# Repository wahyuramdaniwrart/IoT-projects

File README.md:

# Project IoT WRART

## Descriptions
Selamat Datang di project IoT yang saya jalankan, ini merupakan arsip dar setiap project yang sudah saya jalankan, silahkan gunakan dengan sebaik mungkin jika memang source kode yang digunakan pada poject ini bisa bermanfaat unuk anda. project ini menggunakan eagle untuk membuat wiring dan skema rangkaian alatnya.

## Contributing
Kami menyambut semua kontribusi! Berikut ini beberapa cara untuk memulai:
1. Laporkan bug: Jika Anda menemukan bug, harap beri tahu kami. Ajukan masalah dan beri tahu kami masalahnya.
2. Kontribusikan kode: Jika Anda seorang pengembang dan ingin berkontribusi, ikuti petunjuk di bawah ini untuk memulai!
3. Saran: Jika Anda tidak ingin membuat kode tetapi memiliki beberapa ide hebat, ajukan masalah yang menjelaskan beberapa pembaruan atau peningkatan yang ingin Anda lihat!
4. Dokumentasi: Jika Anda merasa perlu beberapa dokumentasi tambahan, jangan ragu untuk menambahkannya!

## Instructions
1. Fork repositori ini
2. Klon repositori yang di-fork
3. Tambahkan kontribusi Anda (kode atau dokumentasi)
4. Commit dan push
5. Tunggu hingga pull request digabungkan

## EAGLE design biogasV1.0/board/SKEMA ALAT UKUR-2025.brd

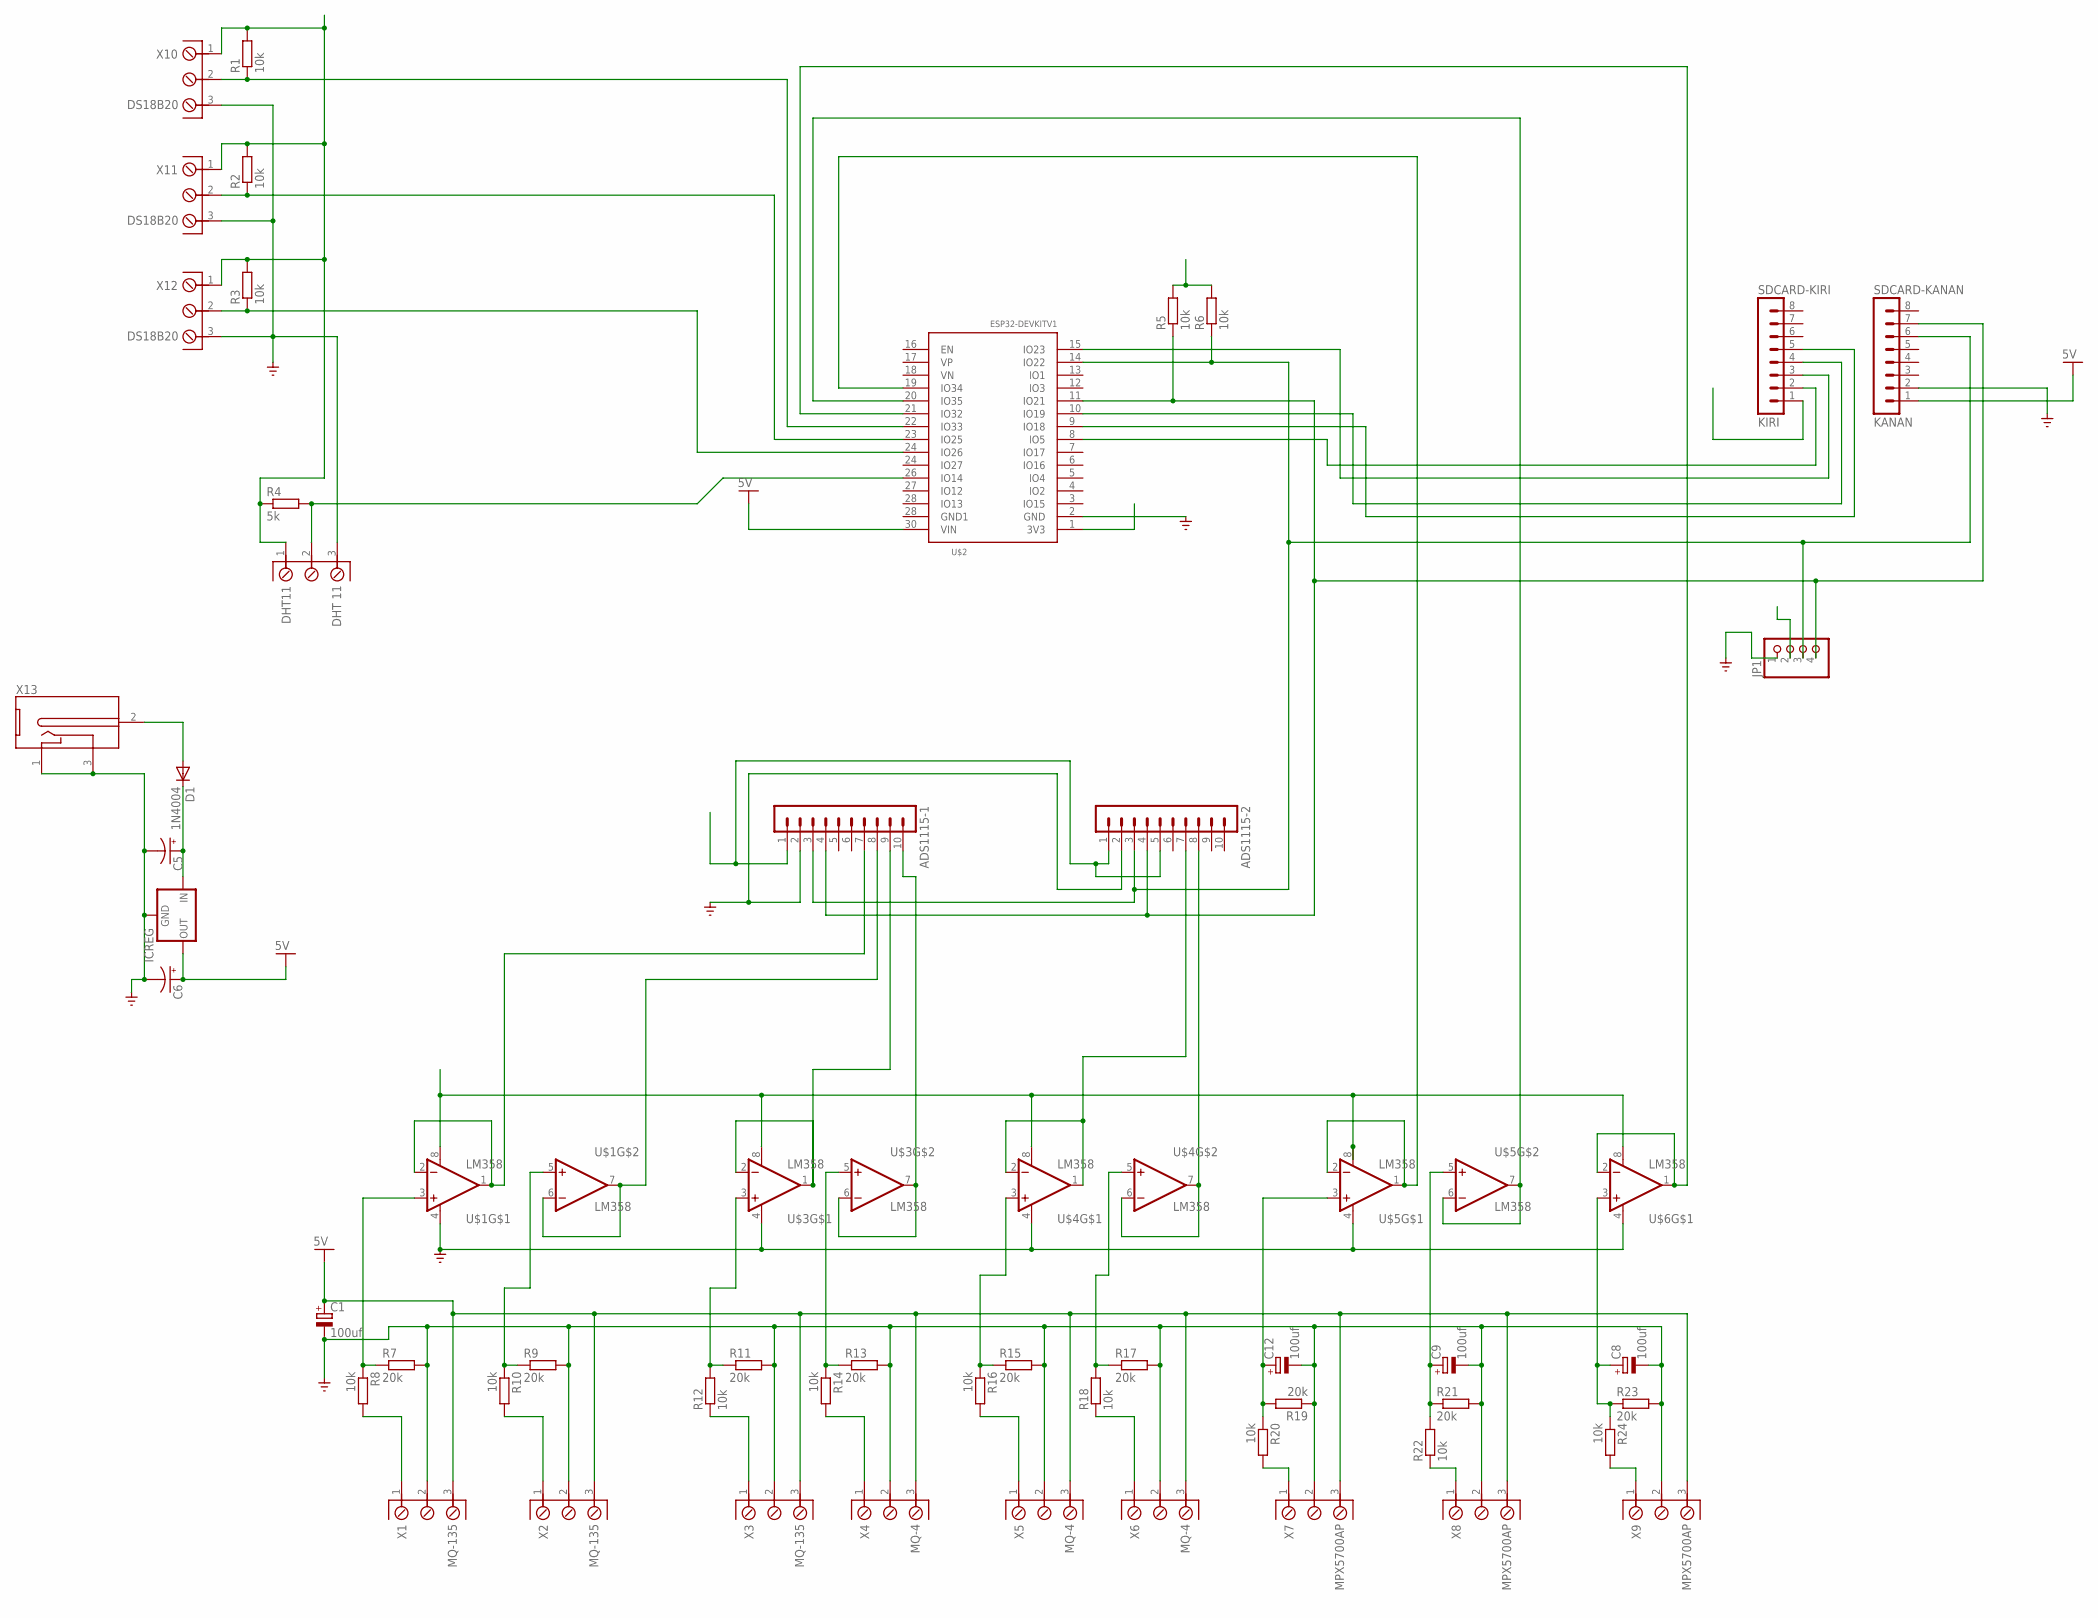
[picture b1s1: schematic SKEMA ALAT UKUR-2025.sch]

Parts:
ADS1115-1, ADS1115-2: MA10-1
C1, C8, C9, C12: 100uf; E5-10,5
C5, C6: CPOL-USE5-13; E5-13
D1: 1N4004; DO41-10
DHT11: DHT 11; AKL701_3_13
ICREG: 78XXS
JP1: PINHD-1X4; 1X04
R1, R2, R3, R5, R6, R8, R10, R12, R14, R16, R18, R20, R22, R24: 10k; 0411/12
R4: 5k; 0411/12
R7, R9, R11, R13, R15, R17, R19, R21, R23: 20k; 0411/12
SDCARD-KANAN: KANAN; MA08-1
SDCARD-KIRI: KIRI; MA08-1
U$1, U$3, U$4, U$5, U$6: LM358; DIP08
U$2: ESP32DEVKITV1; ESP32-DEVKITV1
X1, X2, X3: MQ-135; AKL701_3_13
X4, X5, X6: MQ-4; AKL701_3_13
X7, X8, X9: MPX5700AP; AKL701_3_13
X10, X11, X12: DS18B20; AKL701_3_13
X13: DC-2.1MM-5MM; DC-21MM

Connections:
3.3V: ADS1115-1.1, ADS1115-2.1, ADS1115-2.5, DHT11.1, JP1.2, R1.2, R2.2, R3.2, R4.1, R5.2, R6.2, SDCARD-KIRI.1, U$1.8 (V+), U$2.1 (3V3), U$3.8 (V+), U$4.8 (V+), U$5.8 (V+), U$6.8 (V+), X10.1, X11.1, X12.1
GND: ADS1115-1.2, ADS1115-2.2, C1.-, C5.-, C6.-, C8.-, C9.-, C12.-, DHT11.3, ICREG.GND, JP1.1, R7.2, R9.2, R11.2, R13.2, R15.2, R17.2, R19.1, R21.2, R23.2, SDCARD-KANAN.2, U$1.4 (V-), U$2.2 (GND), U$3.4 (V-), U$4.4 (V-), U$5.4 (V-), U$6.4 (V-), X1.2, X2.2, X3.2, X4.2, X5.2, X6.2, X7.2, X8.2, X9.2, X10.3, X11.3, X12.3, X13.1, X13.3 (2)
unnamed: ADS1115-1.7, U$1.1 (OUT), U$1.2 (-IN)
unnamed: R10.2, X2.1
unnamed: R9.1, R10.1, U$1.5 (+IN)
unnamed: ADS1115-1.8, U$1.6 (-IN), U$1.7 (OUT)
unnamed: ADS1115-1.9, U$3.1 (OUT), U$3.2 (-IN)
unnamed: ADS1115-1.10, U$3.6 (-IN), U$3.7 (OUT)
unnamed: R13.1, R14.1, U$3.5 (+IN)
unnamed: R14.2, X4.1
unnamed: R15.1, R16.1, U$4.3 (+IN)
unnamed: ADS1115-2.7, U$4.1 (OUT), U$4.2 (-IN)
unnamed: ADS1115-2.8, U$4.6 (-IN), U$4.7 (OUT)
unnamed: R17.1, R18.2, U$4.5 (+IN)
unnamed: U$2.19 (IO34), U$5.1 (OUT), U$5.2 (-IN)
unnamed: U$2.20 (IO35), U$5.6 (-IN), U$5.7 (OUT)
unnamed: U$2.21 (IO32), U$6.1 (OUT), U$6.2 (-IN)
unnamed: ADS1115-1.3, ADS1115-2.3, JP1.3, R6.1, SDCARD-KANAN.6, U$2.14 (IO22)
unnamed: R3.1, U$2.24 (IO27), X12.2
unnamed: C8.+, R23.1, R24.1, U$6.3 (+IN)
unnamed: DHT11.2, R4.2, U$2.26 (IO14)
unnamed: ADS1115-1.4, ADS1115-2.4, JP1.4, R5.1, SDCARD-KANAN.7, U$2.11 (IO21)
unnamed: R2.1, U$2.23 (IO25), X11.2
unnamed: R16.2, X5.1
unnamed: R7.1, R8.1, U$1.3 (+IN)
unnamed: SDCARD-KIRI.2, U$2.8 (IO5)
unnamed: R1.1, U$2.22 (IO33), X10.2
unnamed: SDCARD-KIRI.3, U$2.15 (IO23)
unnamed: SDCARD-KIRI.4, U$2.10 (IO19)
unnamed: SDCARD-KIRI.5, U$2.9 (IO18)
unnamed: R8.2, X1.1
unnamed: R12.1, X3.1
unnamed: R11.1, R12.2, U$3.3 (+IN)
unnamed: R18.1, X6.1
unnamed: C12.+, R19.2, R20.1, U$5.3 (+IN)
unnamed: R20.2, X7.1
unnamed: C9.+, R21.1, R22.2, U$5.5 (+IN)
unnamed: R22.1, X8.1
unnamed: R24.2, X9.1
unnamed: C5.+, D1.C, ICREG.IN
unnamed: D1.A, X13.2 (3)
VCC: C1.+, C6.+, ICREG.OUT, SDCARD-KANAN.1, U$2.30 (VIN), X1.3, X2.3, X3.3, X4.3, X5.3, X6.3, X7.3, X8.3, X9.3

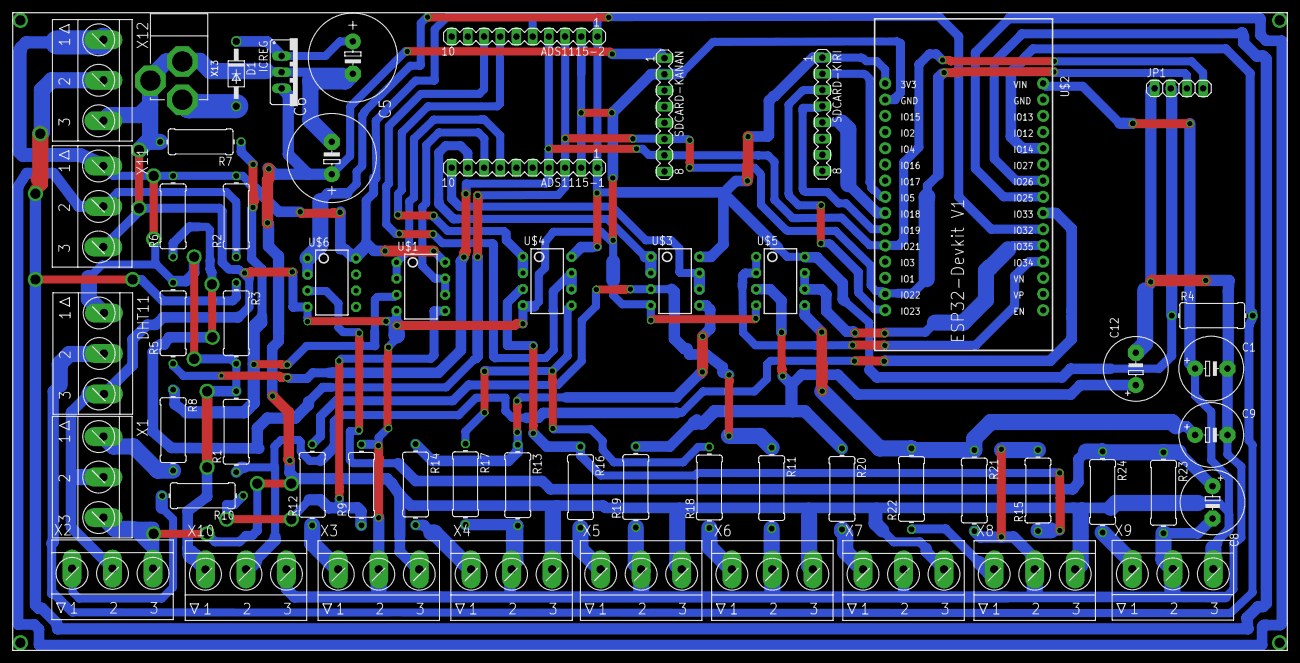
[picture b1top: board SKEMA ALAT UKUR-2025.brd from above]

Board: 2 copper layers, 199.9 x 100.0 mm, 57 parts (0 on the bottom side), 42 nets.

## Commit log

2024-02-03 my code upload
2024-05-22 new file: sapuan lab/project monitoring 1 bulan/monitoring/arduino.ino new file: sapuan lab/project monitoring 1 bulan/monitoring/esp32.ino
2024-07-05 sistem monitoring hidroponik
2024-11-20 Create project-tugas-akhir
    ini adalah kode untuk tugas akhir saya, dimana kode ini terhubung dengan aplikasi blynk-iot untuk memantau nilai dan menjadi kontrol untuk data logger dan juga menjadi webserver unuk dapat mengunduh 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
2024-11-20 Rename project-tugas-akhir to project-tugas-akhir.ino
2025-02-25 Create kode.ino
    kode pertama pada project ini
2025-02-26 Create rawCode.ino
    kode mentah
2025-02-26 Update kode.ino
    penambahan fitur mqtt dan lcd oled di perbaharui
2025-03-03 Add files via upload
    insert design pcb dan wiring alat
2025-03-03 Create gambar.png
    add gambar
2025-03-03 Add files via upload
    penambahasan skema pcb
2025-03-03 Delete biogasV1.0/image/gambar.png
    penghapusan contoh gamabr
2025-03-03 Update kode.ino
    kode perbaikan dan kode yang digunakan pada saat pemasangan alat.
2025-03-03 Create README.md
    deskripsi pertama
2025-03-03 Update README.md
    perbaikan tampilan gamabr
2025-03-03 Create test.ino
    penambahan folder baru
2025-03-03 Add files via upload
    penambahan wiring dan papan pcb dari eagle
2025-03-03 Update README.md
    update terussss
2025-03-20 Update kode.ino
    perubhan pada tekanan
2025-03-23 Create METANE-GAS-3-SENSOR.ino
    settingan kode pebacaan metana
2025-03-23 Add files via upload
    adding files

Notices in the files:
parts and their libraries:
m-pad-2.1: License : GNU General Public License version 2 (see bottom)
